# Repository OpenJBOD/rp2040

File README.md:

# OpenJBOD RP2040 Baseboard

This repository contains the hardware design files OpenJBOD RP2040 Baseboard.

For the accompanying software, please refer to:
- [micropython/micropython](https://github.com/micropython/micropython)
- [OpenJBOD/software](https://github.com/OpenJBOD/software)

## Requirements

- The design was created on KiCad 8.0.2, it uses the default symbol and footprint libraries from it. If you have installed KiCad without the default libraries, you may experience missing symbols.
- Non-standard symbols, footprints and models are bundled in the repository and should load with the project.

## Compatibility

The board is compatible with any standards-compliant ATX power supply.

For SAS expanders, any SAS expander that can operate with only power (i.e. no PCI-e communication) should be functional on the board.

The board has successfully been tested with:

- Adaptec AEC-82885T

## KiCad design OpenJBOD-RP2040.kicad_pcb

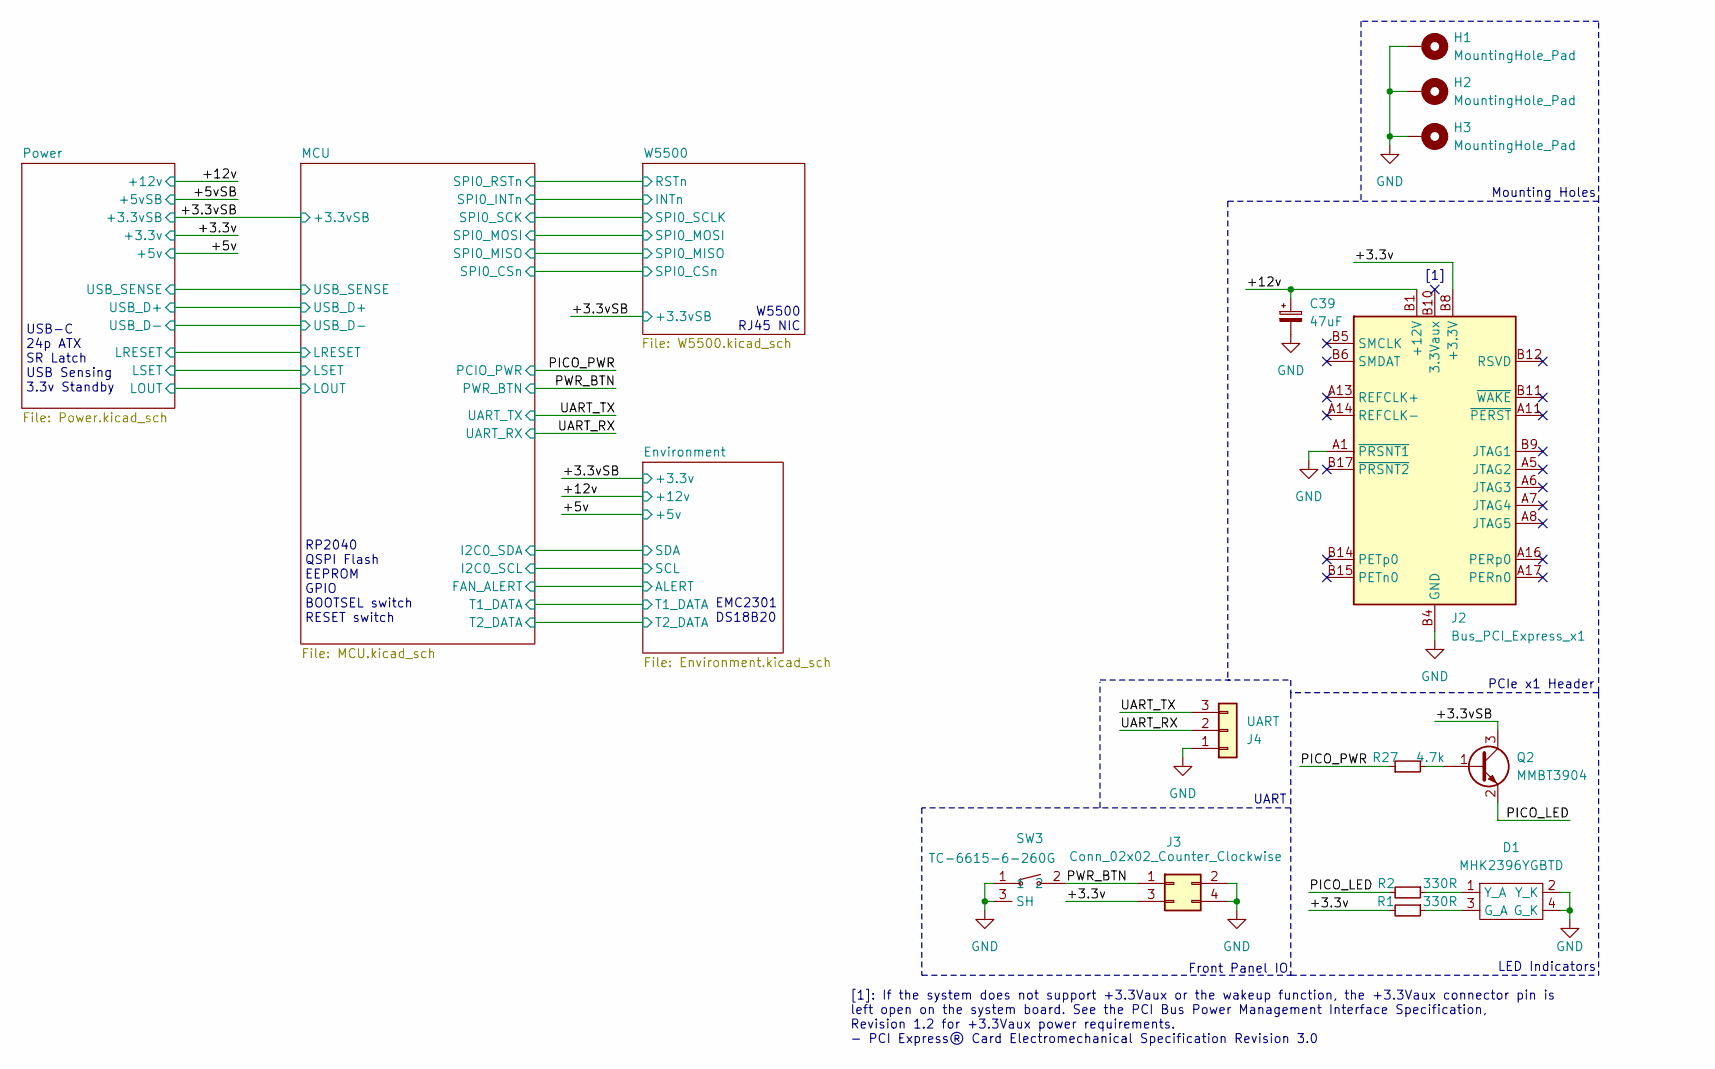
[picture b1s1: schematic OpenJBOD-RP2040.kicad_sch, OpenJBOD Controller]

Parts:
C39: 47uF; CP_Elec_6.3x5.4; LCSC Part # C2836440
D1: MHK2396YGBTD; LED-TH_MHK2396YGBTD; LCSC Part # C2764899
H1, H2, H3: MountingHole_Pad; MountingHole_4.3mm_M4_Pad_Via
J2: Bus_PCI_Express_x1; 91618-11010C; LCSC Part # C5210918
J3: Conn_02x02_Counter_Clockwise; PinHeader_2x02_P2.54mm_Vertical; LCSC Part # C492419
J4: UART; PinHeader_1x03_P2.54mm_Horizontal; LCSC Part # C2894945
Q2: MMBT3904; SOT-23; LCSC Part # C20526
R1, R2: 330R; R_0402_1005Metric; LCSC Part # C25104
R27: 4.7k; R_0402_1005Metric; LCSC Part # C25900
SW3: TC-6615-6-260G; KEY-TH_TC-6615-6-160G; LCSC Part # C2845272

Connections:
/+3.3v: J2.A9 (+3.3V), J2.A10 (+3.3V), J2.B8 (+3.3V), J3.3, R1.2; also elsewhere on the board
/+12v: C39.1, J2.A2 (+12V), J2.A3 (+12V), J2.B1 (+12V), J2.B2 (+12V), J2.B3 (+12V); also elsewhere on the board
/PICO_LED: Q2.2 (E), R2.2
/PICO_PWR: R27.1; also elsewhere on the board
/PWR_BTN: J3.1, SW3.2; also elsewhere on the board
/UART_RX: J4.2; also elsewhere on the board
/UART_TX: J4.3; also elsewhere on the board
GND: C39.2, D1.2 (Y_K), D1.4 (G_K), H1.1, H2.1, H3.1, J2.A1 (~PRSNT1), J2.A4 (GND), J2.A12 (GND), J2.A15 (GND), J2.A18 (GND), J2.B4 (GND), J2.B7 (GND), J2.B13 (GND), J2.B16 (GND), J2.B18 (GND), J3.2, J3.4, J4.1, SW3.1, SW3.3 (SH), SW3.4 (SH); also elsewhere on the board
unnamed: D1.3 (G_A), R1.1
unnamed: D1.1 (Y_A), R2.1
unnamed: Q2.1 (B), R27.2

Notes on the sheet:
UART
RP2040 QSPI Flash EEPROM GPIO BOOTSEL switch RESET switch
Mounting Holes
Front Panel IO
EMC2301 DS18B20
LED Indicators
W5500 RJ45 NIC
USB-C 24p ATX SR Latch USB Sensing 3.3v Standby
PCIe x1 Header
[1]: If the system does not support +3.3Vaux or the wakeup function, the +3.3Vaux connector pin is left open on the system board. See the PCI Bus Power Management Interface Specification, Revision 1.2 for +3.3Vaux power requirements. - PCI Express® Card Electromechanical Specification Revision 3.0
[1]

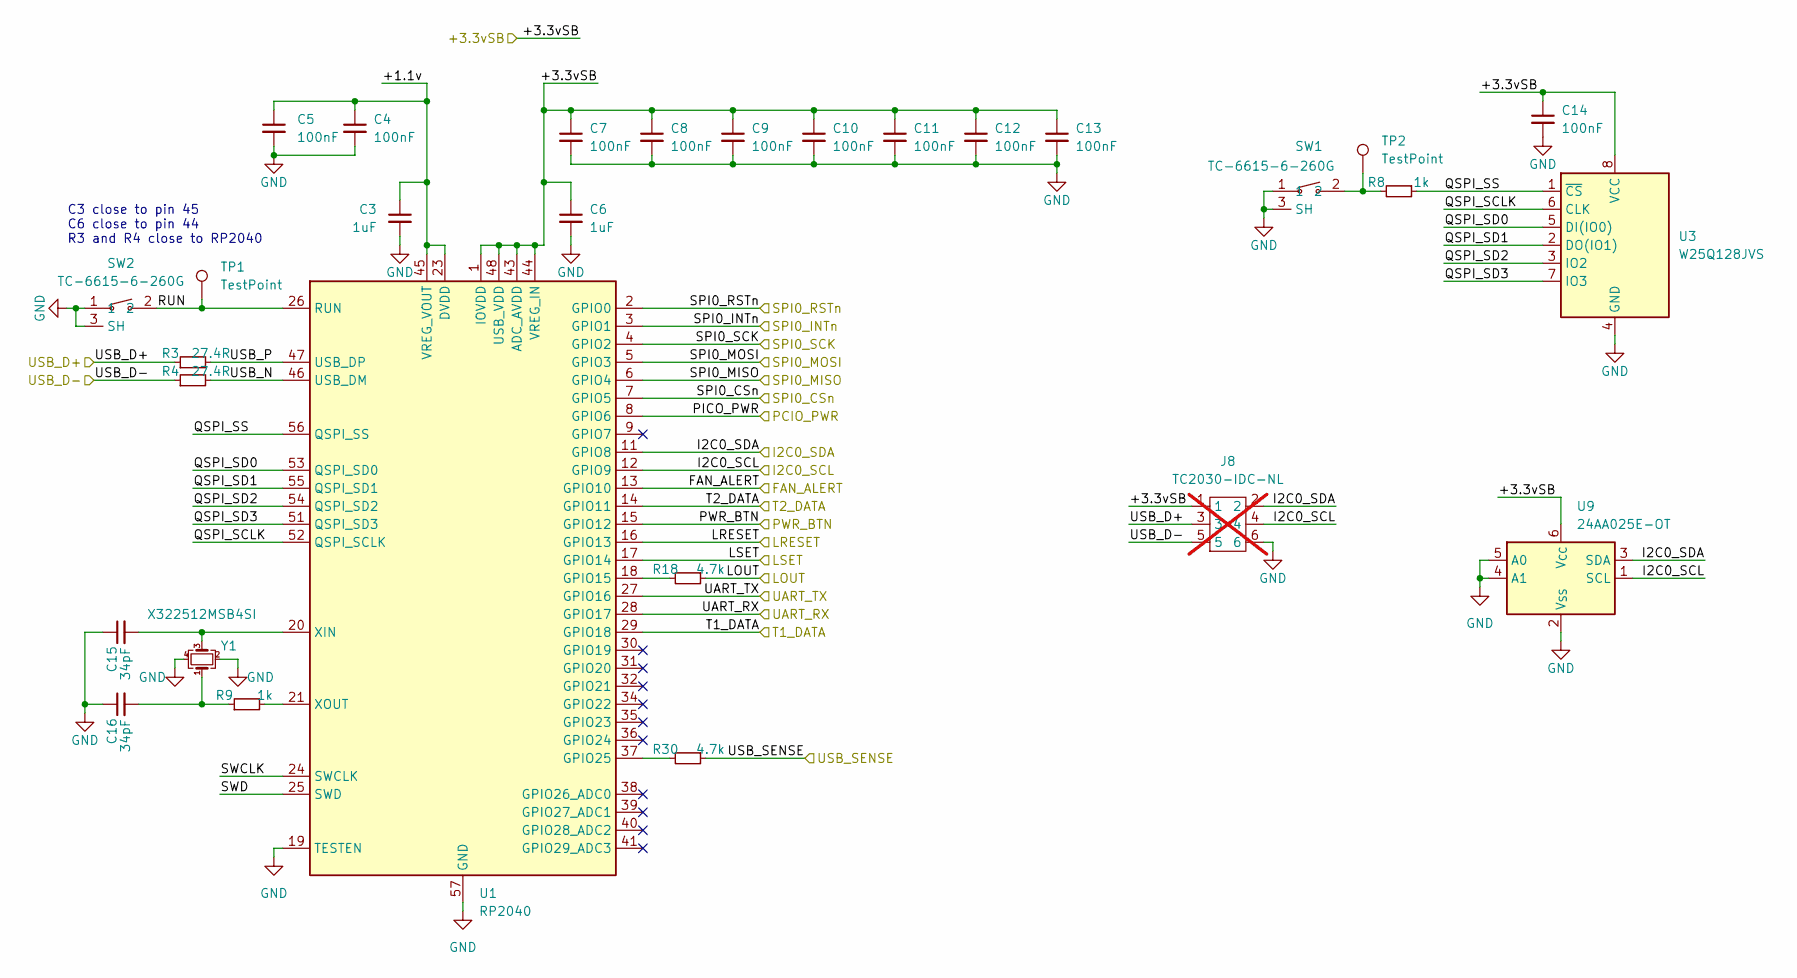
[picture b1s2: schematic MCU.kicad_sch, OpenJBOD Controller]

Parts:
C3, C6: 1uF; C_0402_1005Metric; LCSC Part # C52923
C4, C5, C7, C8, C9, C10, C11, C12, C13, C14: 100nF; C_0402_1005Metric; LCSC Part # C1525
C15, C16: 34pF; C_0603_1608Metric; LCSC Part # C1658
J8: TC2030-IDC-NL; Tag-Connect_TC2030-IDC-NL_2x03_P1.27mm_Vertical; not fitted
R3, R4: 27.4R; R_0402_1005Metric; LCSC Part # C284479
R8, R9: 1k; R_0402_1005Metric; LCSC Part # C11702
R18, R30: 4.7k; R_0402_1005Metric; LCSC Part # C25900
SW1, SW2: TC-6615-6-260G; KEY-TH_TC-6615-6-160G; LCSC Part # C2845272
TP1, TP2: TestPoint; TestPoint_Pad_D1.0mm
U1: RP2040; QFN-56-1EP_7x7mm_P0.4mm_EP3.2x3.2mm; LCSC Part # C2040
U3: W25Q128JVS; SOIC-8_5.23x5.23mm_P1.27mm; LCSC Part # C97521
U9: 24AA025E-OT; SOT-23-6; LCSC Part # C129895
Y1: X322512MSB4SI; Crystal_SMD_3225-4Pin_3.2x2.5mm; LCSC Part # C9002

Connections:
/Environment/ALERT: U1.13 (GPIO10); also elsewhere on the board
/Environment/SCL: J8.4, U1.12 (GPIO9), U9.1 (SCL); also elsewhere on the board
/Environment/SDA: J8.2, U1.11 (GPIO8), U9.3 (SDA); also elsewhere on the board
/Environment/T1_DATA: U1.29 (GPIO18); also elsewhere on the board
/Environment/T2_DATA: U1.14 (GPIO11); also elsewhere on the board
/MCU/+1.1v: C3.1, C4.1, C5.1, U1.23 (DVDD), U1.45 (VREG_VOUT), U1.50 (DVDD)
/MCU/LOUT: R18.1; also elsewhere on the board
/MCU/LRESET: U1.16 (GPIO13); also elsewhere on the board
/MCU/LSET: U1.17 (GPIO14); also elsewhere on the board
/MCU/QSPI_SCLK: U1.52 (QSPI_SCLK), U3.6 (CLK)
/MCU/QSPI_SD0: U1.53 (QSPI_SD0), U3.5 (DI(IO0))
/MCU/QSPI_SD1: U1.55 (QSPI_SD1), U3.2 (DO(IO1))
/MCU/QSPI_SD2: U1.54 (QSPI_SD2), U3.3 (IO2)
/MCU/QSPI_SD3: U1.51 (QSPI_SD3), U3.7 (IO3)
/MCU/QSPI_SS: R8.1, U1.56 (QSPI_SS), U3.1 (~CS)
/MCU/RUN: SW2.2, TP1.1, U1.26 (RUN)
/MCU/SPI0_CSn: U1.7 (GPIO5); also elsewhere on the board
/MCU/SPI0_INTn: U1.3 (GPIO1); also elsewhere on the board
/MCU/SPI0_MISO: U1.6 (GPIO4); also elsewhere on the board
/MCU/SPI0_MOSI: U1.5 (GPIO3); also elsewhere on the board
/MCU/SPI0_RSTn: U1.2 (GPIO0); also elsewhere on the board
/MCU/SPI0_SCK: U1.4 (GPIO2); also elsewhere on the board
/MCU/SWCLK: U1.24 (SWCLK)
/MCU/SWD: U1.25 (SWD)
/MCU/USB_D+: J8.3, R3.1; also elsewhere on the board
/MCU/USB_D-: J8.5, R4.1; also elsewhere on the board
/MCU/USB_N: R4.2, U1.46 (USB_DM)
/MCU/USB_P: R3.2, U1.47 (USB_DP)
/MCU/USB_SENSE: R30.1; also elsewhere on the board
/PICO_PWR: U1.8 (GPIO6); also elsewhere on the board
/PWR_BTN: U1.15 (GPIO12); also elsewhere on the board
/UART_RX: U1.28 (GPIO17); also elsewhere on the board
/UART_TX: U1.27 (GPIO16); also elsewhere on the board
GND: C3.2, C4.2, C5.2, C6.2, C7.2, C8.2, C9.2, C10.2, C11.2, C12.2, C13.2, C14.2, C15.1, C16.1, J8.6, SW1.1, SW1.3 (SH), SW1.4 (SH), SW2.1, SW2.3 (SH), SW2.4 (SH), U1.19 (TESTEN), U1.57 (GND), U3.4 (GND), U9.2 (V_{SS}), U9.4 (A1), U9.5 (A0), Y1.2, Y1.4; also elsewhere on the board
unnamed: C16.2, R9.1, Y1.1
unnamed: R8.2, SW1.2, TP2.1
unnamed: R18.2, U1.18 (GPIO15)
unnamed: R30.2, U1.37 (GPIO25)
unnamed: C15.2, U1.20 (XIN), Y1.3
unnamed: R9.2, U1.21 (XOUT)

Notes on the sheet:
C3 close to pin 45 C6 close to pin 44 R3 and R4 close to RP2040

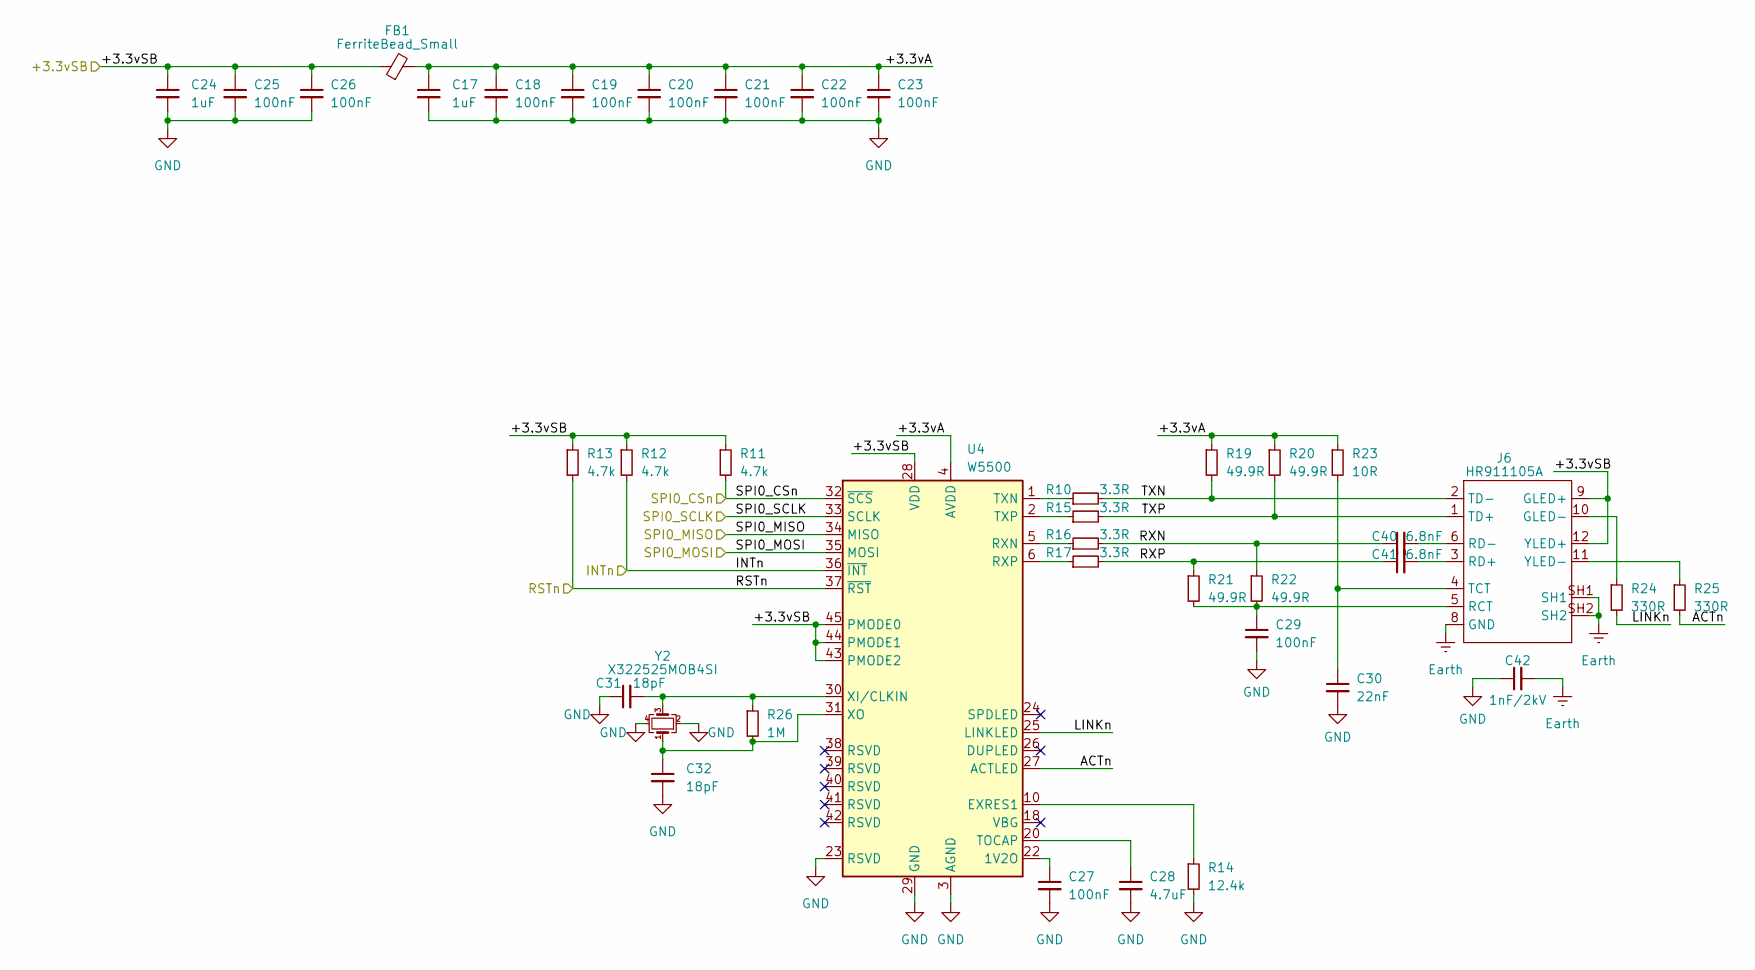
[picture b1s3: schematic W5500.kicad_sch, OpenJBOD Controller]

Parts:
C17, C24: 1uF; C_0402_1005Metric; JLCPCB_PN C52923
C18, C19, C20, C21, C22, C23, C25, C26, C27, C29: 100nF; C_0402_1005Metric; JLCPCB_PN C1525
C28: 4.7uF; C_0402_1005Metric; JLCPCB_PN C23733
C30: 22nF; C_0402_1005Metric; JLCPCB_PN C1532
C31, C32: 18pF; C_0402_1005Metric; JLCPCB_PN C1549
C40, C41: 6.8nF; C_0402_1005Metric; JLCPCB_PN C1542
C42: 1nF/2kV; C_1206_3216Metric; JLCPCB_PN C9196
FB1: FerriteBead_Small; C_0805_2012Metric_Pad1.18x1.45mm_HandSolder; JLCPCB_PN C1015
J6: HR911105A; RJ45-TH_HR911105A; JLCPCB_PN C12074
R10, R15, R16, R17: 3.3R; R_0603_1608Metric; JLCPCB_PN C2930016
R11, R12, R13: 4.7k; R_0402_1005Metric; JLCPCB_PN C25900
R14: 12.4k; R_0402_1005Metric; JLCPCB_PN C11692
R19, R20, R21, R22: 49.9R; R_0402_1005Metric; JLCPCB_PN C25120
R23: 10R; R_0402_1005Metric; JLCPCB_PN C25077
R24, R25: 330R; R_0402_1005Metric; JLCPCB_PN C25104
R26: 1M; R_0402_1005Metric; JLCPCB_PN C26083
U4: W5500; LQFP-48_7x7mm_P0.5mm; JLCPCB_PN C32843
Y2: X322525MOB4SI; Crystal_SMD_3225-4Pin_3.2x2.5mm; JLCPCB_PN C9006

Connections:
/MCU/SPI0_CSn: R11.2, U4.32 (~SCS); also elsewhere on the board
/MCU/SPI0_INTn: R12.2, U4.36 (~INT); also elsewhere on the board
/MCU/SPI0_MISO: U4.34 (MISO); also elsewhere on the board
/MCU/SPI0_MOSI: U4.35 (MOSI); also elsewhere on the board
/MCU/SPI0_RSTn: R13.2, U4.37 (~RST); also elsewhere on the board
/MCU/SPI0_SCK: U4.33 (SCLK); also elsewhere on the board
/W5500/+3.3vA: C17.1, C18.1, C19.1, C20.1, C21.1, C22.1, C23.1, FB1.2, R19.1, R20.1, R23.1, U4.4 (AVDD), U4.8 (AVDD), U4.11 (AVDD), U4.15 (AVDD), U4.17 (AVDD), U4.21 (AVDD)
/W5500/ACTn: R25.2, U4.27 (ACTLED)
/W5500/LINKn: R24.2, U4.25 (LINKLED)
/W5500/RXN: C40.1, R16.2, R22.1
/W5500/RXP: C41.1, R17.2, R21.1
/W5500/TXN: J6.2 (TD-), R10.2, R19.2
/W5500/TXP: J6.1 (TD+), R15.2, R20.2
Earth: C42.2, J6.8 (GND), J6.SH1, J6.SH2
GND: C17.2, C18.2, C19.2, C20.2, C21.2, C22.2, C23.2, C24.2, C25.2, C26.2, C27.2, C28.2, C29.2, C30.2, C31.1, C32.2, C42.1, R14.2, U4.3 (AGND), U4.9 (AGND), U4.14 (AGND), U4.16 (AGND), U4.19 (AGND), U4.23 (RSVD), U4.29 (GND), U4.48 (AGND), Y2.2, Y2.4; also elsewhere on the board
unnamed: J6.10 (GLED-), R24.1
unnamed: C29.1, J6.5 (RCT), R21.2, R22.2
unnamed: C41.2, J6.3 (RD+)
unnamed: C40.2, J6.6 (RD-)
unnamed: C30.1, J6.4 (TCT), R23.2
unnamed: J6.11 (YLED-), R25.1
unnamed: C27.1, U4.22 (1V2O)
unnamed: R14.1, U4.10 (EXRES1)
unnamed: R16.1, U4.5 (RXN)
unnamed: R17.1, U4.6 (RXP)
unnamed: C28.1, U4.20 (TOCAP)
unnamed: R10.1, U4.1 (TXN)
unnamed: R15.1, U4.2 (TXP)
unnamed: C31.2, R26.1, U4.30 (XI/CLKIN), Y2.3
unnamed: C32.1, R26.2, U4.31 (XO), Y2.1

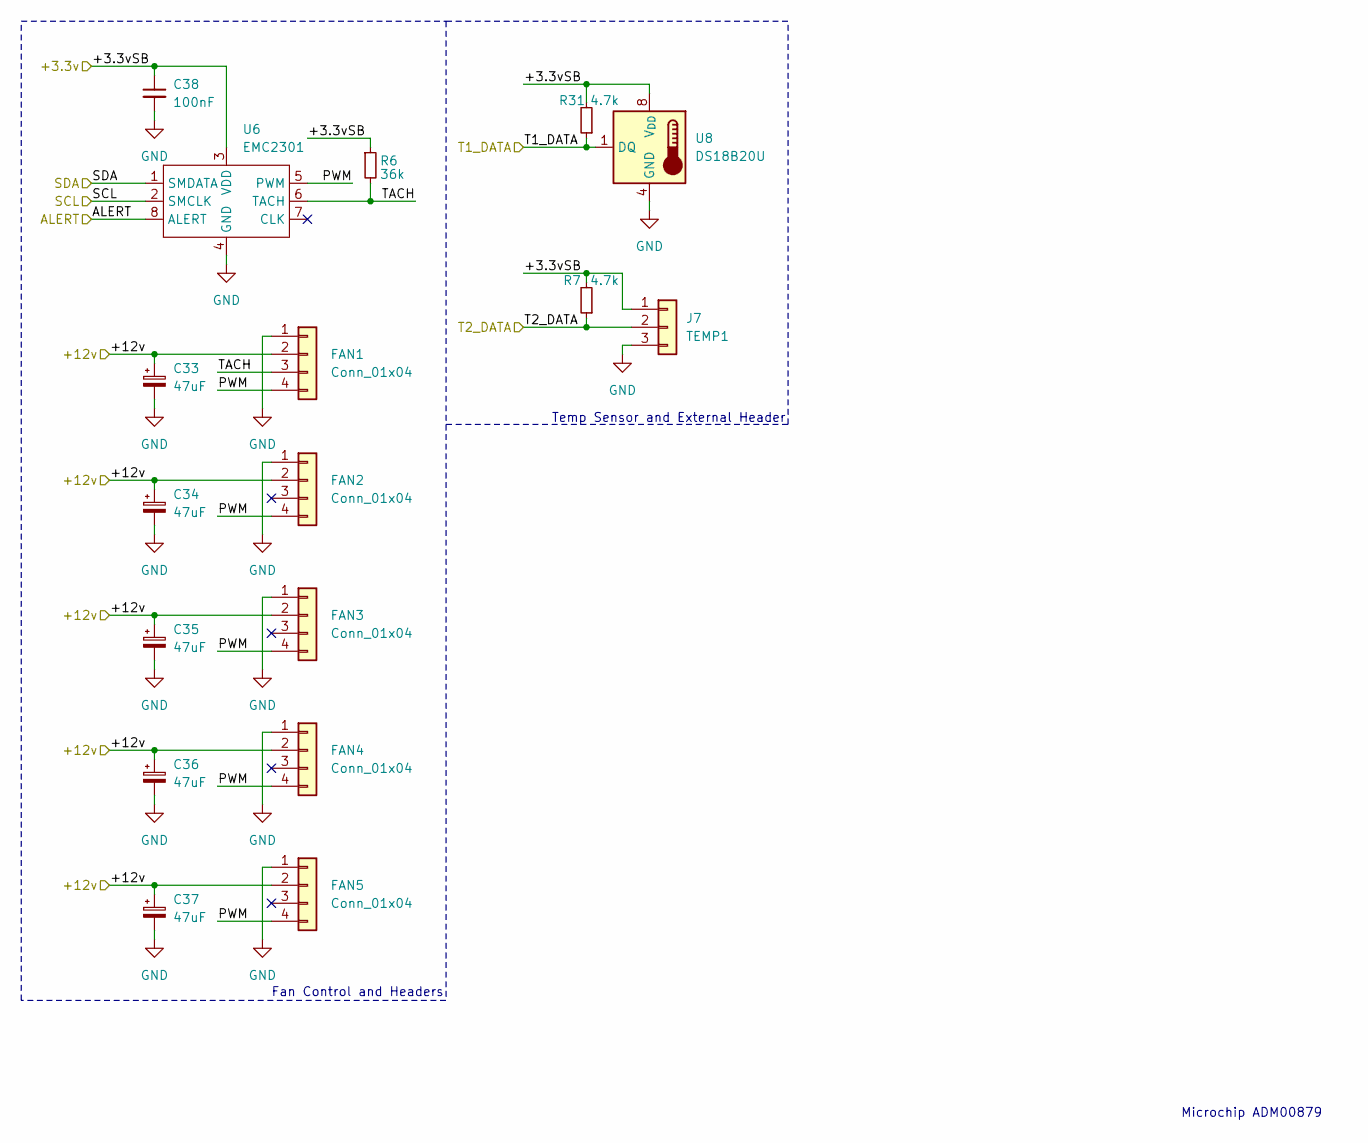
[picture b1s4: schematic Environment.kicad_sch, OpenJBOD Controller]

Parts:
C33, C34, C35, C36, C37: 47uF; CP_Elec_6.3x5.4; JLCPCB_PN C2836440
C38: 100nF; C_0402_1005Metric; JLCPCB_PN C1525
FAN1, FAN2, FAN3, FAN4, FAN5: Conn_01x04; FanPinHeader_1x04_P2.54mm_Vertical; JLCPCB_PN C240840
J7: TEMP1; PinHeader_1x03_P2.54mm_Vertical; JLCPCB_PN C49257
R6: 36k; R_0402_1005Metric; JLCPCB_PN C25744
R7, R31: 4.7k; R_0402_1005Metric; JLCPCB_PN C25900
U6: EMC2301; MSOP-8_3x3mm_P0.65mm; JLCPCB_PN C148036
U8: DS18B20U; MSOP-8_3x3mm_P0.65mm; JLCPCB_PN C695836

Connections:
/+12v: C33.1, C34.1, C35.1, C36.1, C37.1, FAN1.2, FAN2.2, FAN3.2, FAN4.2, FAN5.2; also elsewhere on the board
/Environment/ALERT: U6.8 (ALERT); also elsewhere on the board
/Environment/SCL: U6.2 (SMCLK); also elsewhere on the board
/Environment/SDA: U6.1 (SMDATA); also elsewhere on the board
/Environment/T1_DATA: R31.1, U8.1 (DQ); also elsewhere on the board
/Environment/T2_DATA: J7.2, R7.1; also elsewhere on the board
GND: C33.2, C34.2, C35.2, C36.2, C37.2, C38.2, FAN1.1, FAN2.1, FAN3.1, FAN4.1, FAN5.1, J7.3, U6.4 (GND), U8.4 (GND); also elsewhere on the board

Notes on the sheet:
Temp Sensor and External Header
Microchip ADM00879
Fan Control and Headers

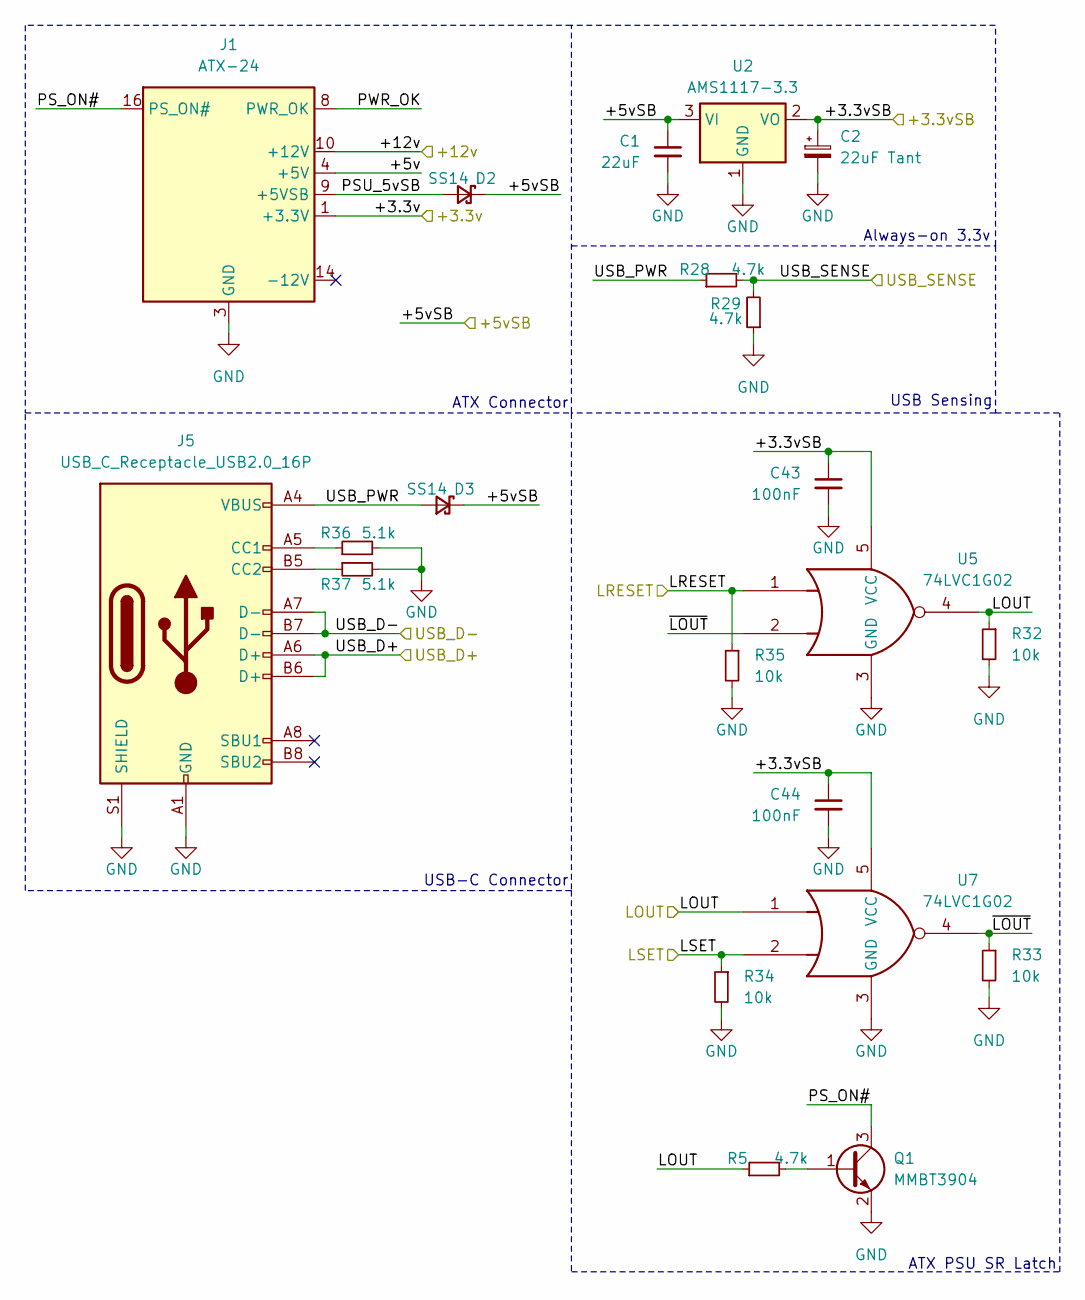
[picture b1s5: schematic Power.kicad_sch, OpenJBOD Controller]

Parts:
C1: 22uF; C_1206_3216Metric; JLCPCB_PN C12891
C2: 22uF Tant; CP_EIA-3216-18_Kemet-A; JLCPCB_PN C11366
C43, C44: 100nF; C_0402_1005Metric; JLCPCB_PN C1525
D2, D3: SS14; D_SMA; JLCPCB_PN C2480
J1: ATX-24; CONN-TH_M4202V-2X12P; JLCPCB_PN C492535
J5: USB_C_Receptacle_USB2.0_16P; USB-C-SMD_TYPE-C16PIN; JLCPCB_PN C393939
Q1: MMBT3904; SOT-23; JLCPCB_PN C20526
R5, R28, R29: 4.7k; R_0402_1005Metric; JLCPCB_PN C25900
R32, R33, R34, R35: 10k; C_0402_1005Metric
R36, R37: 5.1k; C_0402_1005Metric
U2: AMS1117-3.3; SOT-223-3_TabPin2; JLCPCB_PN C6186
U5, U7: 74LVC1G02; SOT-353_SC-70-5; JLCPCB_PN C353856

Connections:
/+3.3v: J1.1 (+3.3V), J1.2 (+3.3V), J1.12 (+3.3V), J1.13 (+3.3V); also elsewhere on the board
/+5v: J1.4 (+5V), J1.6 (+5V), J1.21 (+5V), J1.22 (+5V), J1.23 (+5V); also elsewhere on the board
/+5vSB: C1.1, D2.1 (K), D3.1 (K), U2.3 (VI)
/+12v: J1.10 (+12V), J1.11 (+12V); also elsewhere on the board
/MCU/LOUT: R5.1, R32.1, U5.4, U7.1; also elsewhere on the board
/MCU/LRESET: R35.1, U5.1; also elsewhere on the board
/MCU/LSET: R34.1, U7.2; also elsewhere on the board
/MCU/USB_D+: J5.A6 (D+), J5.B6 (D+); also elsewhere on the board
/MCU/USB_D-: J5.A7 (D-), J5.B7 (D-); also elsewhere on the board
/MCU/USB_SENSE: R28.2, R29.2; also elsewhere on the board
/Power/PSU_5vSB: D2.2 (A), J1.9 (+5VSB)
/Power/PS_ON#: J1.16 (PS_ON#), Q1.3 (C)
/Power/PWR_OK: J1.8 (PWR_OK)
/Power/USB_PWR: D3.2 (A), J5.A4 (VBUS), J5.A9 (VBUS), J5.B4 (VBUS), J5.B9 (VBUS), R28.1
/Power/~LOUT: R33.1, U5.2, U7.4
GND: C1.2, C2.2, C43.2, C44.2, J1.3 (GND), J1.5 (GND), J1.7 (GND), J1.15 (GND), J1.17 (GND), J1.18 (GND), J1.19 (GND), J1.24 (GND), J5.A1 (GND), J5.A12 (GND), J5.B1 (GND), J5.B12 (GND), J5.S1 (SHIELD), Q1.2 (E), R29.1, R32.2, R33.2, R34.2, R35.2, R36.2, R37.2, U2.1 (GND), U5.3 (GND), U7.3 (GND); also elsewhere on the board
unnamed: J5.A5 (CC1), R36.1
unnamed: J5.B5 (CC2), R37.1
unnamed: Q1.1 (B), R5.2

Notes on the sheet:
USB-C Connector
ATX PSU SR Latch
ATX Connector
USB Sensing
Always-on 3.3v

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
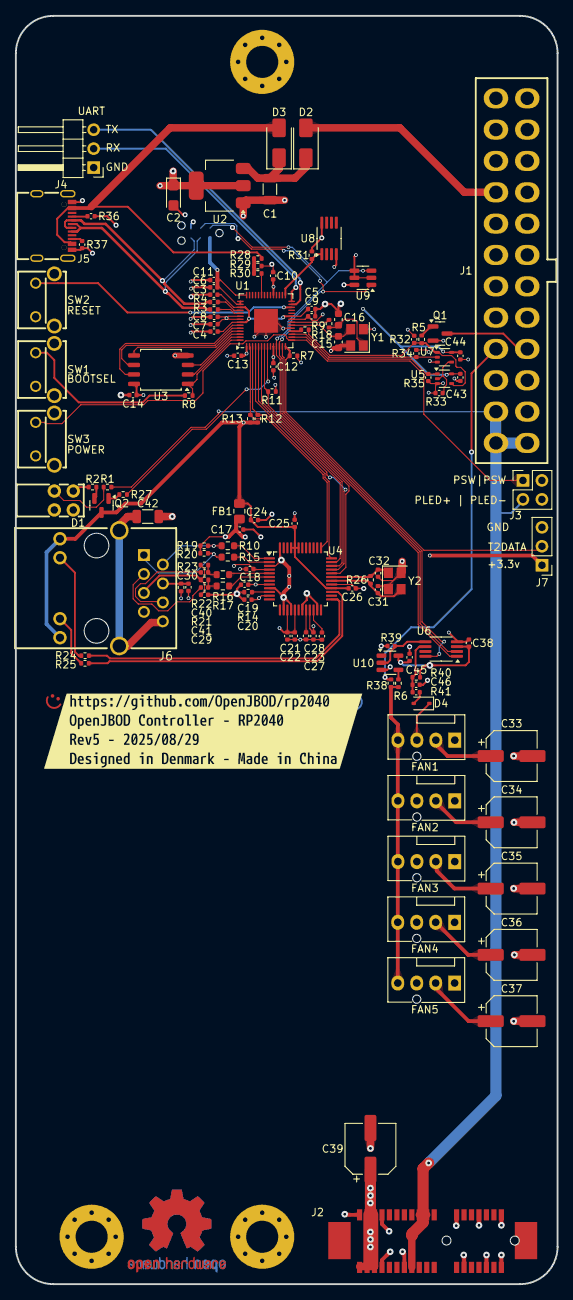
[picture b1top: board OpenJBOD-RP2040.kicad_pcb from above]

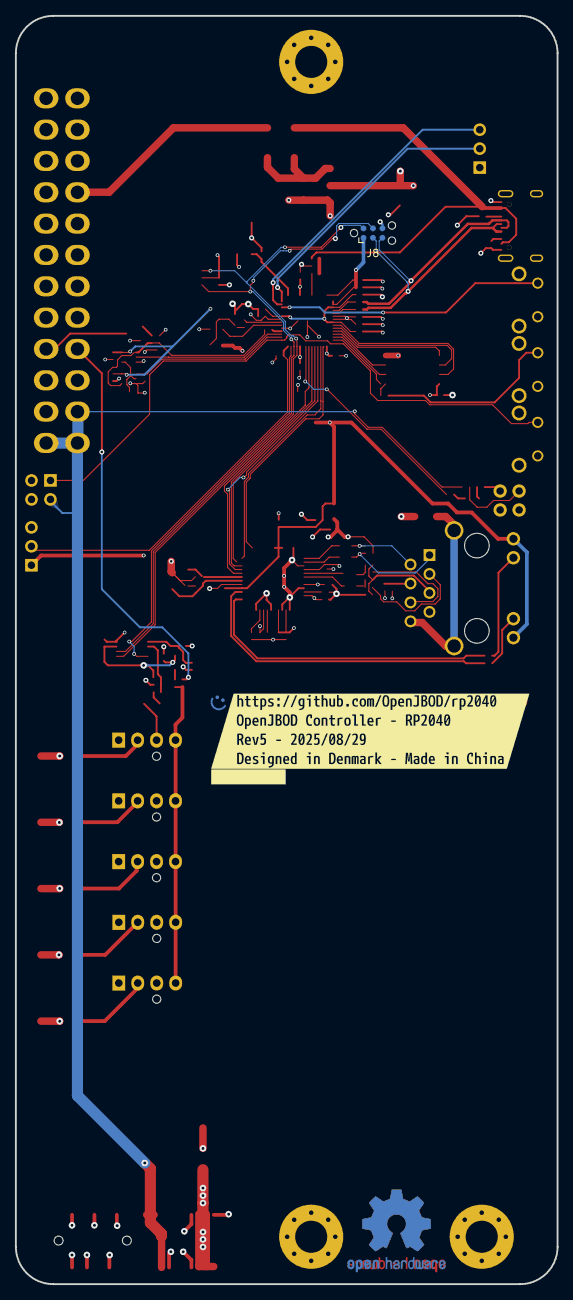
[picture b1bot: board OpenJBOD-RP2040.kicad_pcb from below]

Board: 4 copper layers, 72.6 x 170.0 mm, 127 parts (2 on the bottom side), 83 nets.

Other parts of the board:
C45: 100nF; C_0402_1005Metric
C46: 22nF; C_0402_1005Metric
D4: SDMK0340L; D_SOD-323
R38, R40: 4.7k; R_0402_1005Metric
R39: 100k; C_0402_1005Metric
R41: 100R; C_0402_1005Metric
U10: 74LVC1G07; SOT-23-5
kibuzzard-68B1B45A: G***; kibuzzard-68B1B45A
kibuzzard-68B1B461: G***; kibuzzard-68B1B461

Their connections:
/+5v: R38.1; also elsewhere on the board
GND: C45.2, C46.2, R39.2, U10.3 (GND); also elsewhere on the board
unnamed: D4.2 (A), R41.2

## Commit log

2024-08-18 initial board upload
2024-08-18 add license
2024-08-18 added uart header
2024-08-18 remove serial number graphic in favor of digital sn
2024-08-29 Rev4
    Bunch of small changes, namely:
    Add onboard DS18B20 probe for more accurate temp readings without external hardware.
    Rename T1DATA to T2DATA to still allow external probes.
    Add USB power sensing circuit.
    Add SR latch for PS_ON# handling
    Add J4 UART header.
2024-09-11 rev4 order version added side-mounted IO to the panel so an IO shield could theoretically be made added step models cleaned up footprints
2024-09-11 SAS expander compatibility
2024-09-12 add ci
2024-09-12 update ci to run on rev* tags
2024-09-18 update ATX header for better solderability
2024-09-18 adjust UART header and rotate R27 for cleaner layout
2024-09-27 replace USB micro B with USB C, requires cleanup
2024-10-30 rev4.2
    Updated silkscreen info block
    Changed microUSB header to MicroXNJ
    Added RoHS and WEEE marking
    Moved BOOTSEL to rear IO
    Moved SR latch
    Moved J3 and J9 closer to the board edge, this helps to not interrupt
2024-12-06 added pulldowns to SR latch pins
2024-12-06 usb-c schematic changes
2024-12-09 pcb: usb-c, pull-downs
2024-12-09 sch/pcb: SR latch caps
2024-12-29 schematic cleanup
2025-08-29 rev5
    Added MACROM (specific ROM holding MAC address and (optionally) board
    revision)
    Added more circuitry to protect the EMC2301, allowing for use with fans
    with internal pull-ups.
    Added USB-C
2025-08-29 Update CI
